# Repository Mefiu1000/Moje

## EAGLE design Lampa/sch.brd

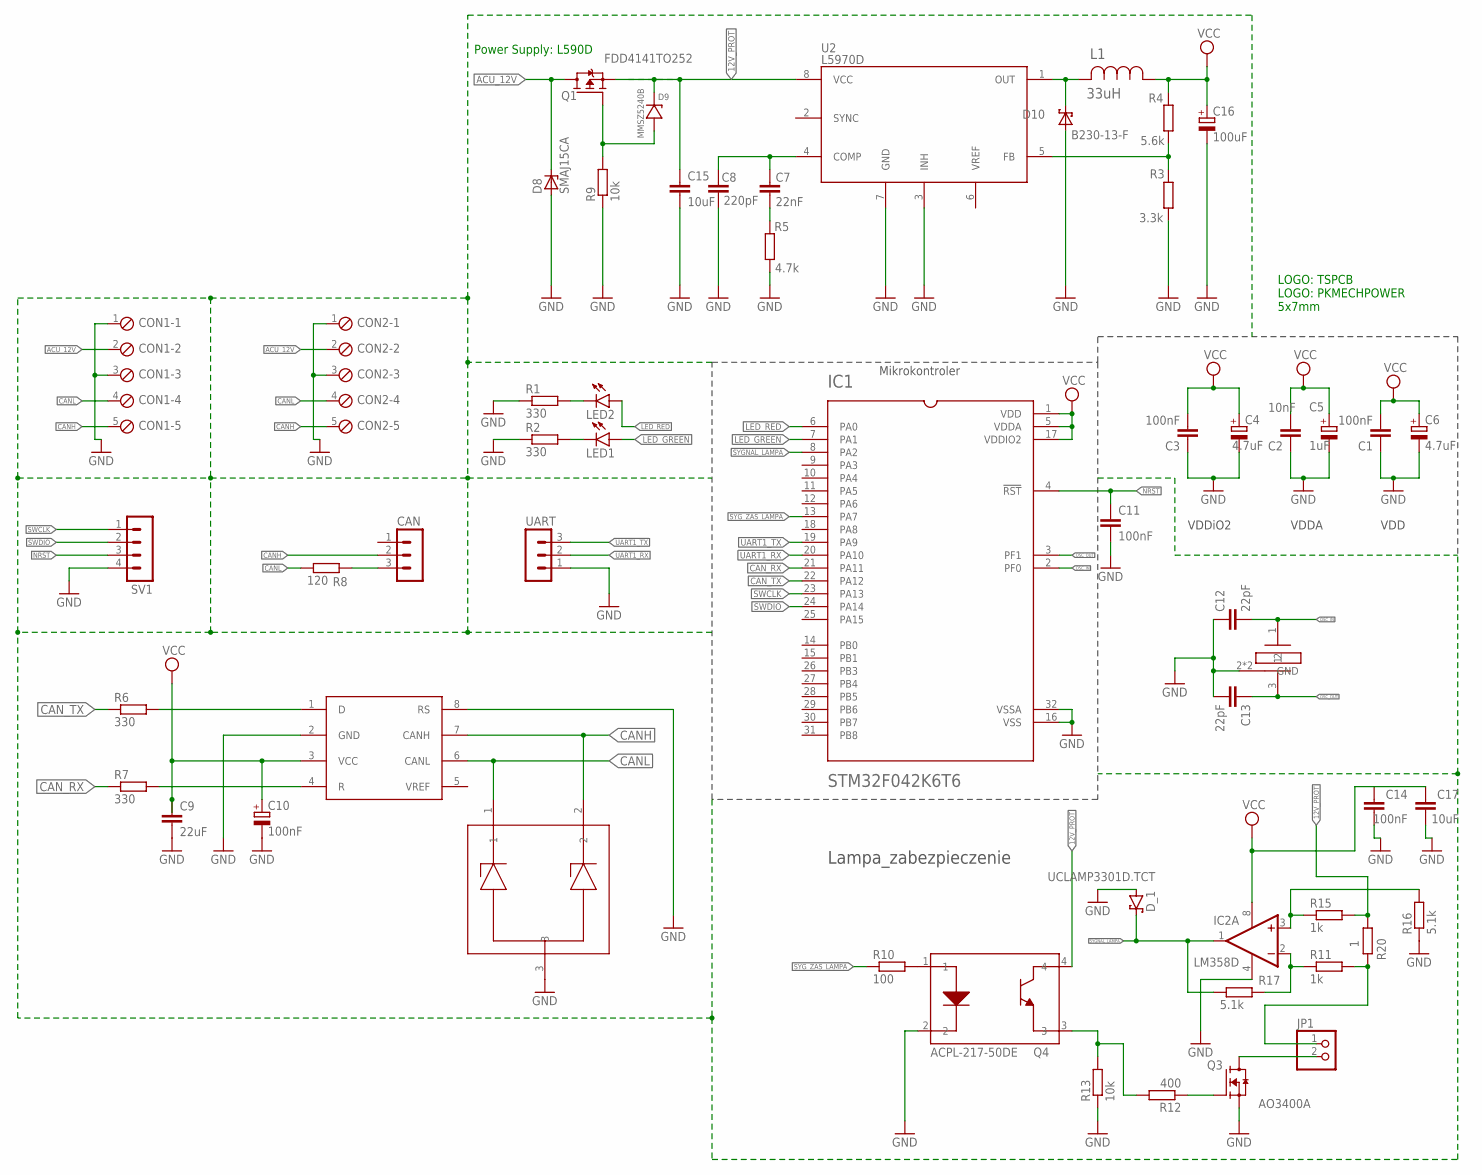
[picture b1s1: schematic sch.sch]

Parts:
C1, C3, C11, C14: 100nF; C0805
C2: 10nF; C0805
C4, C6: 4.7uF; SMC_C
C5: 1uF; SMC_C
C7: 22nF; C0805
C8: 220pF; C0805
C9: 22uF; C0805
C10: 100nF; SMC_C
C12, C13: 22pF; C0805
C15: 10uF; C1210
C16: 100uF; SMC_D
C17: 10uF; C0805
CAN: MA03-1
CON1, CON2: MPT5; 5POL254
D8: SMAJ15CA; SMA
D9: MMSZ5240B; SOD123
D10: B230-13-F; SMB
D_1: UCLAMP3301D.TCT; SOD323
IC1: STM32F042K6T6; QFP80P900X900X160-32N
IC2: LM358D; SO08
JP1: PINHD-1X2; 1X02
L1: 33uH; INDM125125X600N
LED1, LED2: LEDCHIP-LED0805; CHIP-LED0805
Q1: FDD4141TO252; TO252
Q3: AO3400A; SOT95P280X125-3N
Q4: ACPL-217-50DE; SOIC127P700X220-4N
R1, R2: 330; R0805
R3: 3.3k; R0805
R4: 5.6k; R0805
R5: 4.7k; R0805
R6, R7: 330; M0805
R8: 120; M0805
R9: 10k; R0805
R10: 100; M0805
R11, R15: 1k; M0805
R12: 400; M0805
R13: 10k; M0805
R16, R17: 5.1k; M0805
R20: 1; R2512
SV1: MA04-1
U2: L5970D; SO-8
U$1: SN65HVD; SO8
U$2: PESD3V3S2UT_; SOT95P230X110-3N
UART: MA03-1
XTAL1: CRYSTAL_SMDXT-324; XT-324

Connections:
12V_PROT: C15.1, D9.1, Q1.2 (S), Q4.4, R15.2, R20.2, U2.8 (VCC)
ACU_12V: CON1.2, CON2.2, D8.1 (K), Q1.3 (D)
CANH: CAN.2, CON1.5, CON2.5, U$1.7 (CANH), U$2.2
CANL: CON1.4, CON2.4, R8.1, U$1.6 (CANL), U$2.1
CAN_RX: IC1.21 (PA11), R7.1
CAN_TX: IC1.22 (PA12), R6.1
GND: C1.1, C2.1, C3.1, C4.-, C5.-, C6.-, C8.1, C9.2, C10.-, C11.2, C12.1, C13.2, C14.1, C15.2, C16.-, C17.1, CON1.1, CON1.3, CON2.1, CON2.3, D8.2 (A), D10.2 (A), D_1.1 (A), IC1.16 (VSS), IC1.32 (VSSA), IC2.4 (V-), Q3.2 (S), Q4.2, R1.1, R2.1, R3.1, R5.1, R9.1, R13.1, R16.1, SV1.4, U2.3 (INH), U2.7 (GND), U$1.2 (GND), U$1.8 (RS), U$2.3, UART.1, XTAL1.2 (GND), XTAL1.4 (GND)
LED_GREEN: IC1.7 (PA1), LED1.A
LED_RED: IC1.6 (PA0), LED2.A
unnamed: R6.2, U$1.1 (D)
unnamed: R7.2, U$1.4 (R)
unnamed: LED2.C, R1.2
unnamed: LED1.C, R2.2
unnamed: JP1.2, Q3.3 (D)
unnamed: CAN.3, R8.2
unnamed: D9.2, Q1.1 (G), R9.2
unnamed: IC2.3 (+IN), R15.1, R16.2
unnamed: Q4.1, R10.2
unnamed: Q3.1 (G), R12.1
unnamed: D10.1 (K), L1.2, U2.1 (OUT)
unnamed: Q4.3, R12.2, R13.2
unnamed: R3.2, R4.1, U2.5 (FB)
unnamed: IC2.2 (-IN), R11.1, R17.2
unnamed: JP1.1, R11.2, R20.1
unnamed: C7.2, C8.2, U2.4 (COMP)
unnamed: C7.1, R5.2
NRST: C11.1, IC1.4 (!RST), SV1.3
OSC_IN: C12.2, IC1.2 (PF0), XTAL1.1
OSC_OUT: C13.1, IC1.3 (PF1), XTAL1.3 (2)
SWCLK: IC1.23 (PA13), SV1.1
SWDIO: IC1.24 (PA14), SV1.2
SYGNAL_LAMPA: D_1.2 (C), IC1.8 (PA2), IC2.1 (OUT), R17.1
SYG_ZAS_LAMPA: IC1.13 (PA7), R10.1
UART1_RX: IC1.20 (PA10), UART.2
UART1_TX: IC1.19 (PA9), UART.3
VCC: C1.2, C2.2, C3.2, C4.+, C5.+, C6.+, C9.1, C10.+, C14.2, C16.+, C17.2, IC1.1 (VDD), IC1.5 (VDDA), IC1.17 (VDDIO2), IC2.8 (V+), L1.1, R4.2, U$1.3 (VCC)

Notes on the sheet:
Mikrokontroler
VDDiO2
VDDA
VDD
Power Supply: L590D
Lampa_zabezpieczenie
LOGO: TSPCB LOGO: PKMECHPOWER 5x7mm

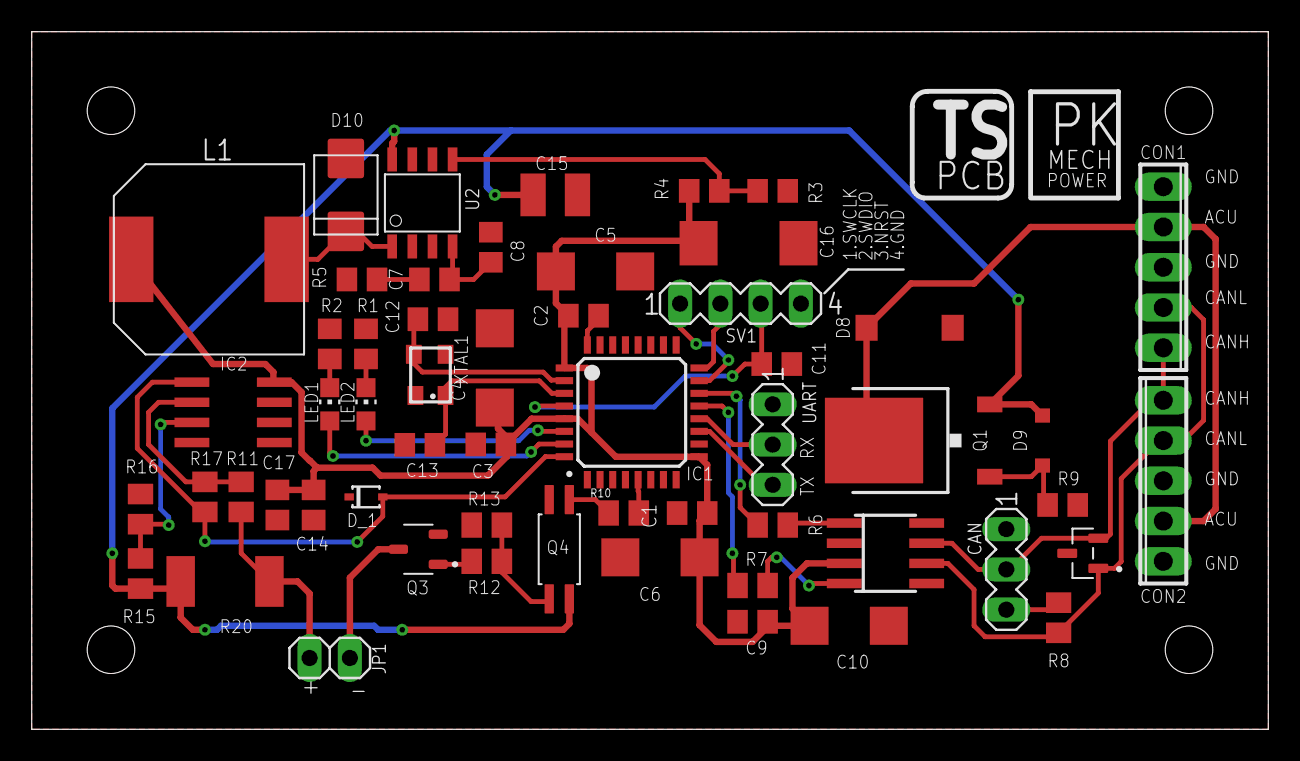
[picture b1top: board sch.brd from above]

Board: 2 copper layers, 78.0 x 44.0 mm, 56 parts (0 on the bottom side), 36 nets.
